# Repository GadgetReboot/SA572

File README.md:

# SA572
SA572 Compander Breakout Board

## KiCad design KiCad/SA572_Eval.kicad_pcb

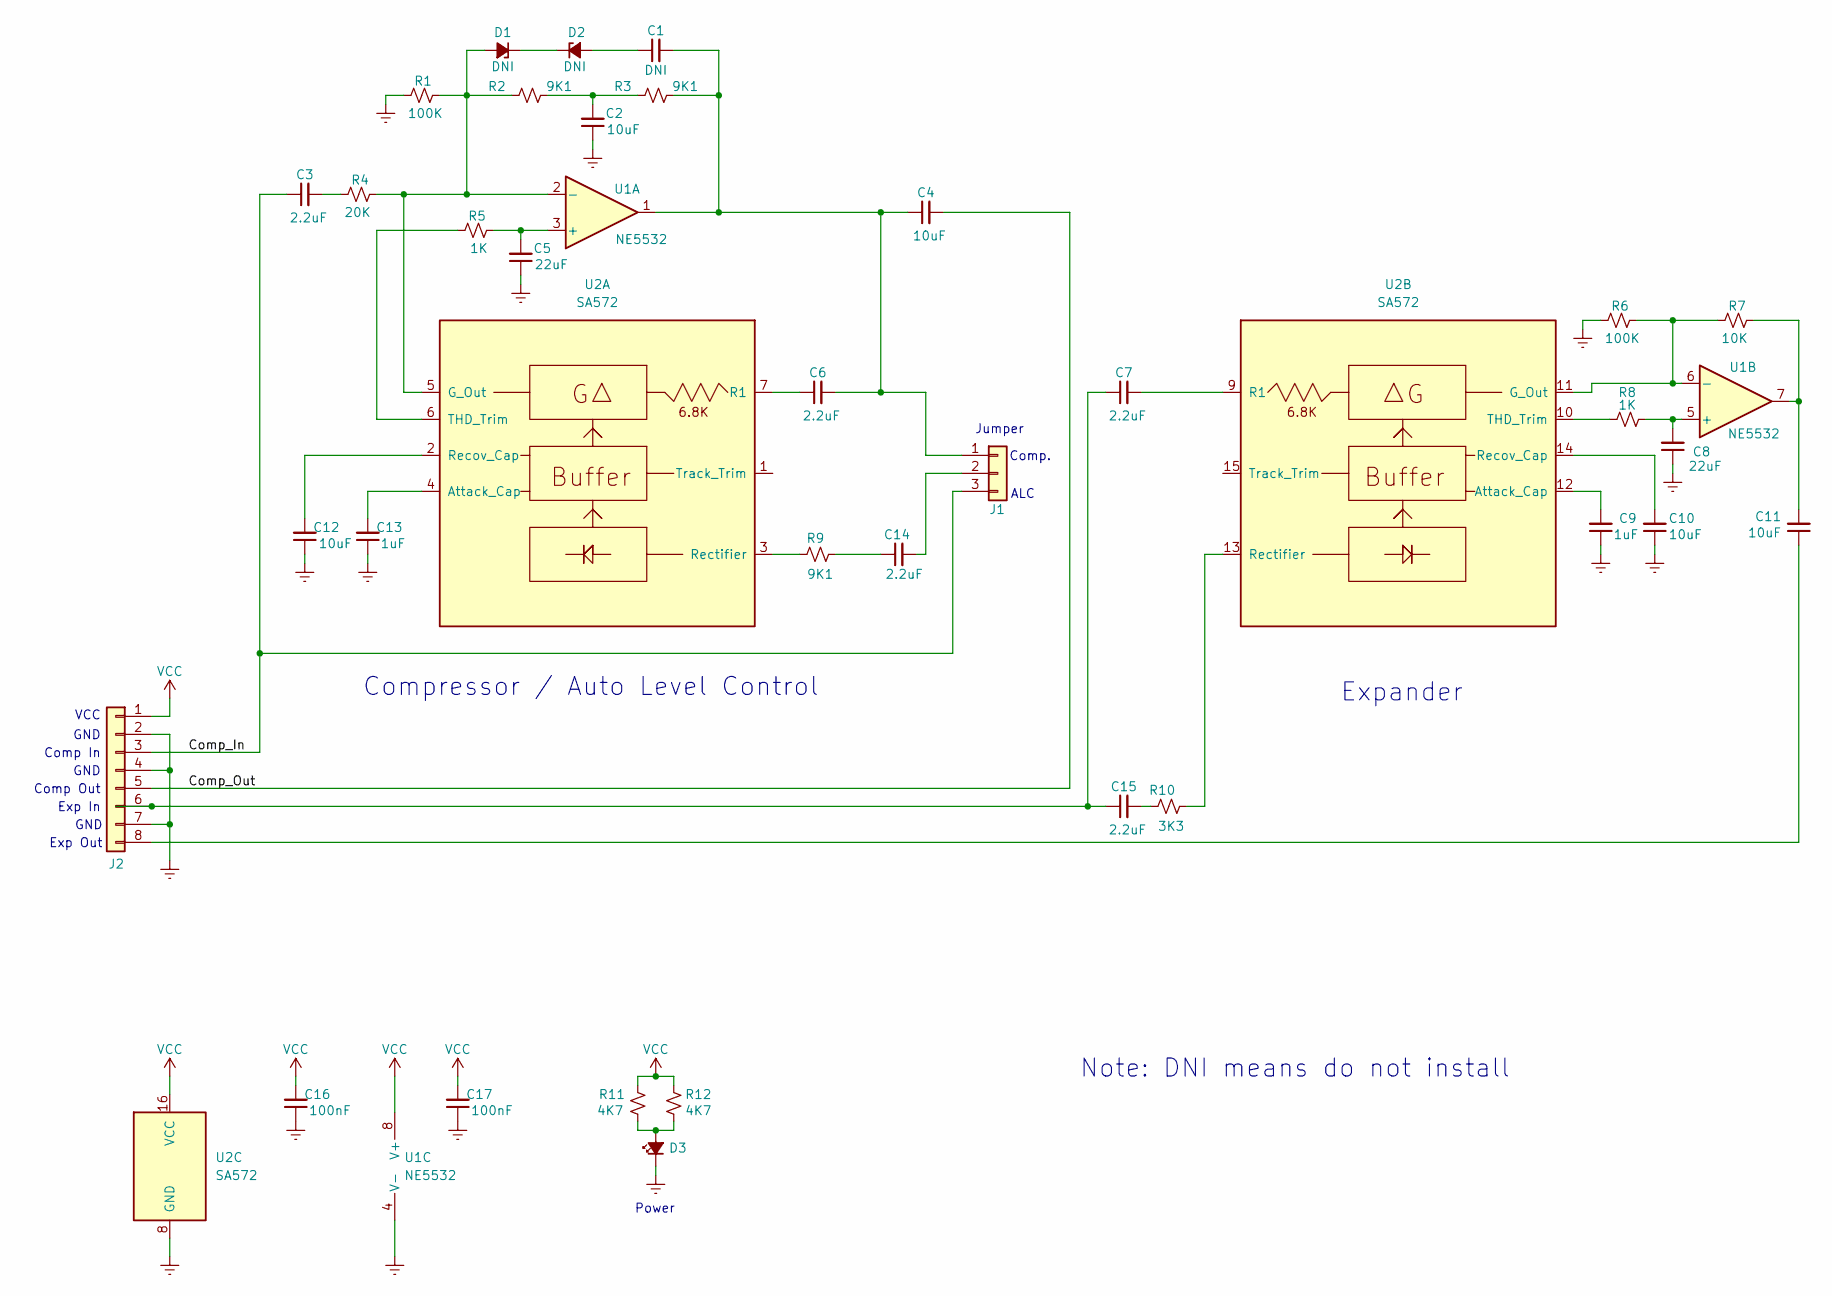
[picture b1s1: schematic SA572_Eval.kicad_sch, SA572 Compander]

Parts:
C1: DNI; C_0805_2012Metric_Pad1.18x1.45mm_HandSolder
C2, C4, C10, C11, C12: 10uF; C_0805_2012Metric_Pad1.18x1.45mm_HandSolder
C3, C6, C7, C14, C15: 2.2uF; C_0805_2012Metric_Pad1.18x1.45mm_HandSolder
C5, C8: 22uF; C_0805_2012Metric_Pad1.18x1.45mm_HandSolder
C9, C13: 1uF; C_0805_2012Metric_Pad1.18x1.45mm_HandSolder
C16, C17: 100nF; C_0805_2012Metric_Pad1.18x1.45mm_HandSolder
D1, D2: DNI; Zener_MiniMELF
D3: LED_Small_Filled; LED_0805_2012Metric_Pad1.15x1.40mm_HandSolder
J1: Conn_01x03; PinHeader_1x03_P2.54mm_Vertical
J2: Conn_01x08; PinHeader_1x08_P2.54mm_Vertical
R1, R6: 100K; R_0805_2012Metric_Pad1.20x1.40mm_HandSolder
R2, R3, R9: 9K1; R_0805_2012Metric_Pad1.20x1.40mm_HandSolder
R4: 20K; R_0805_2012Metric_Pad1.20x1.40mm_HandSolder
R5, R8: 1K; R_0805_2012Metric_Pad1.20x1.40mm_HandSolder
R7: 10K; R_0805_2012Metric_Pad1.20x1.40mm_HandSolder
R10: 3K3; R_0805_2012Metric_Pad1.20x1.40mm_HandSolder
R11, R12: 4K7; R_0805_2012Metric_Pad1.20x1.40mm_HandSolder
U1: NE5532; SOIC-8_3.9x4.9mm_P1.27mm
U2: SA572; SOIC-16W_7.5x10.3mm_P1.27mm

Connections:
/Comp_In: C3.1, J1.3, J2.3
/Comp_Out: C4.2, J2.5
GNDREF: C2.1, C5.1, C8.1, C9.1, C10.1, C12.1, C13.1, C16.1, C17.1, D3.1 (K), J2.2, J2.4, J2.7, R1.1, R6.1, U1.4 (V-), U2.8 (GND)
unnamed: C2.2, R2.2, R3.1
unnamed: C3.2, R4.1
unnamed: C11.2, R7.2, U1.7
unnamed: C14.1, R9.2
unnamed: C15.2, R10.1
unnamed: D1.2 (A), R1.2, R2.1, R4.2, U1.2 (-), U2.5 (G_Out)
unnamed: D1.1 (K), D2.1 (K)
unnamed: C1.1, D2.2 (A)
unnamed: D3.2 (A), R11.2, R12.2
unnamed: C1.2, C4.1, C6.2, J1.1, R3.2, U1.1
unnamed: C14.2, J1.2
unnamed: C7.1, C15.1, J2.6
unnamed: C11.1, J2.8
unnamed: C5.2, R5.2, U1.3 (+)
unnamed: C8.2, R8.2, U1.5 (+)
unnamed: R6.2, R7.1, U1.6 (-), U2.11 (G_Out)
unnamed: C13.2, U2.4 (Attack_Cap)
unnamed: C6.1, U2.7 (R1)
unnamed: C12.2, U2.2 (Recov_Cap)
unnamed: R9.1, U2.3 (Rectifier)
unnamed: R5.1, U2.6 (THD_Trim)
unnamed: C9.2, U2.12 (Attack_Cap)
unnamed: C7.2, U2.9 (R1)
unnamed: C10.2, U2.14 (Recov_Cap)
unnamed: R10.2, U2.13 (Rectifier)
unnamed: R8.1, U2.10 (THD_Trim)
VCC: C16.2, C17.2, J2.1, R11.1, R12.1, U1.8 (V+), U2.16 (VCC)

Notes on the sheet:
Note: DNI means do not install
Exp Out
Comp Out
GND
ALC
Comp In
Jumper
Expander
Comp.
Power
Compressor / Auto Level Control
VCC
Exp In

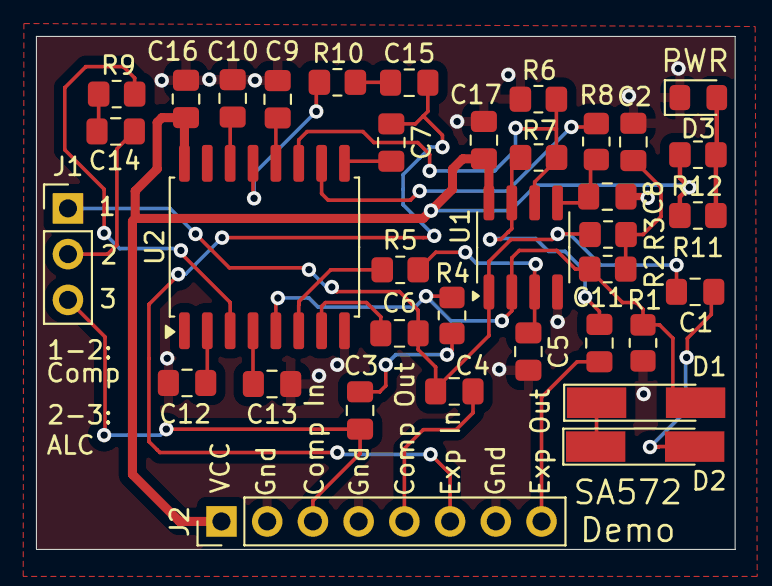
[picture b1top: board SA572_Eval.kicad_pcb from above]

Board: 2 copper layers, 38.8 x 28.5 mm, 36 parts (0 on the bottom side), 30 nets.
